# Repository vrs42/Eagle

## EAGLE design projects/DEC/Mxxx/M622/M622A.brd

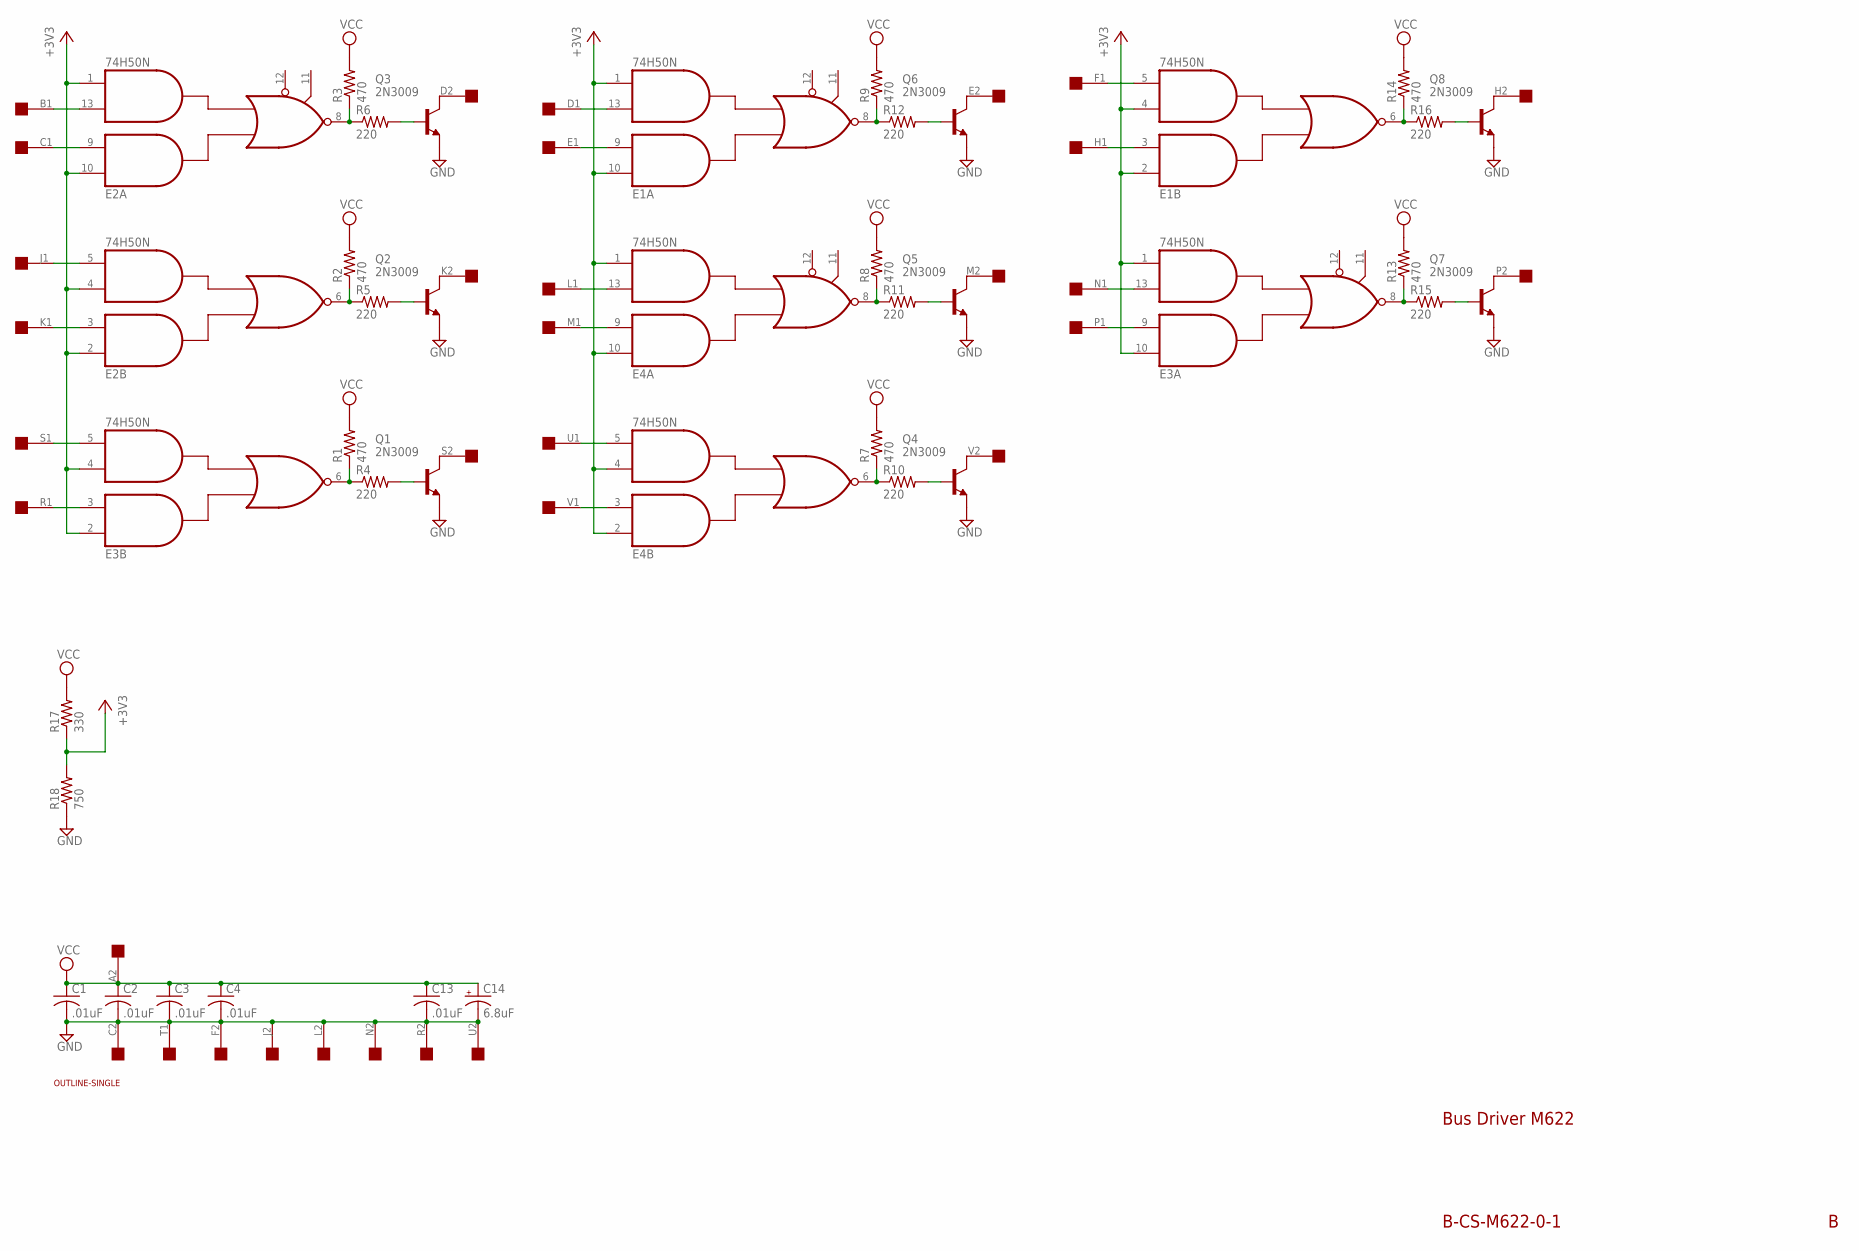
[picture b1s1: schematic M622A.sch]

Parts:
C1, C2, C3, C4, C13: .01uF; C050-025X075
C14: 6.8uF; E12-8
E1, E2, E3, E4: 74H50N; DIL14
Q1, Q2, Q3, Q4, Q5, Q6, Q7, Q8: 2N3009; TO5
R1, R2, R3, R7, R8, R9, R13, R14: 470; 0207/10
R4, R5, R6, R10, R11, R12, R15, R16: 220; 0207/10
R17: 330; 0207/10
R18: 750; 0207/10
U$1: SINGLE; EDGE-CON2
U$4: OUTLINE-SINGLE; SINGLE

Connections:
+3V3: E1.1 (I4), E1.2 (I1), E1.4 (I3), E1.10 (I1), E2.1 (I4), E2.2 (I1), E2.4 (I3), E2.10 (I1), E3.1 (I4), E3.2 (I1), E3.4 (I3), E3.10 (I1), E4.1 (I4), E4.2 (I1), E4.4 (I3), E4.10 (I1), R17.1, R18.2
GND: C1.2, C2.2, C3.2, C4.2, C13.2, C14.-, E1.7 (GND), E2.7 (GND), E3.7 (GND), E4.7 (GND), Q1.1 (E), Q2.1 (E), Q3.1 (E), Q4.1 (E), Q5.1 (E), Q6.1 (E), Q7.1 (E), Q8.1 (E), R18.1, U$1.C2, U$1.F2, U$1.J2, U$1.L2, U$1.N2, U$1.R2, U$1.T1, U$1.U2
unnamed: E2.3 (I2), U$1.K1
unnamed: E2.5 (I4), U$1.J1
unnamed: E2.9 (I2), U$1.C1
unnamed: E2.13 (I3), U$1.B1
unnamed: E3.5 (I4), U$1.S1
unnamed: E3.3 (I2), U$1.R1
unnamed: E2.8 (O), R3.1, R6.1
unnamed: Q3.2 (B), R6.2
unnamed: E1.8 (O), R9.1, R12.1
unnamed: Q6.2 (B), R12.2
unnamed: Q3.3 (C), U$1.D2
unnamed: E2.6 (O), R2.1, R5.1
unnamed: Q6.3 (C), U$1.E2
unnamed: E4.3 (I2), U$1.V1
unnamed: E4.5 (I4), U$1.U1
unnamed: E4.13 (I3), U$1.L1
unnamed: E4.9 (I2), U$1.M1
unnamed: Q2.2 (B), R5.2
unnamed: E1.6 (O), R14.1, R16.1
unnamed: Q8.2 (B), R16.2
unnamed: E4.8 (O), R8.1, R11.1
unnamed: Q5.2 (B), R11.2
unnamed: E3.8 (O), R13.1, R15.1
unnamed: Q7.2 (B), R15.2
unnamed: E3.6 (O), R1.1, R4.1
unnamed: Q1.2 (B), R4.2
unnamed: E4.6 (O), R7.1, R10.1
unnamed: Q4.2 (B), R10.2
unnamed: E1.13 (I3), U$1.D1
unnamed: E1.9 (I2), U$1.E1
unnamed: Q5.3 (C), U$1.M2
unnamed: Q4.3 (C), U$1.V2
unnamed: E1.5 (I4), U$1.F1
unnamed: E3.9 (I2), U$1.P1
unnamed: E3.13 (I3), U$1.N1
unnamed: E1.3 (I2), U$1.H1
unnamed: Q8.3 (C), U$1.H2
unnamed: Q7.3 (C), U$1.P2
unnamed: Q1.3 (C), U$1.S2
unnamed: Q2.3 (C), U$1.K2
VCC: C1.1, C2.1, C3.1, C4.1, C13.1, C14.+, E1.14 (VCC), E2.14 (VCC), E3.14 (VCC), E4.14 (VCC), R1.2, R2.2, R3.2, R7.2, R8.2, R9.2, R13.2, R14.2, R17.2, U$1.A2

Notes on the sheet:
Bus Driver M622
B-CS-M622-0-1

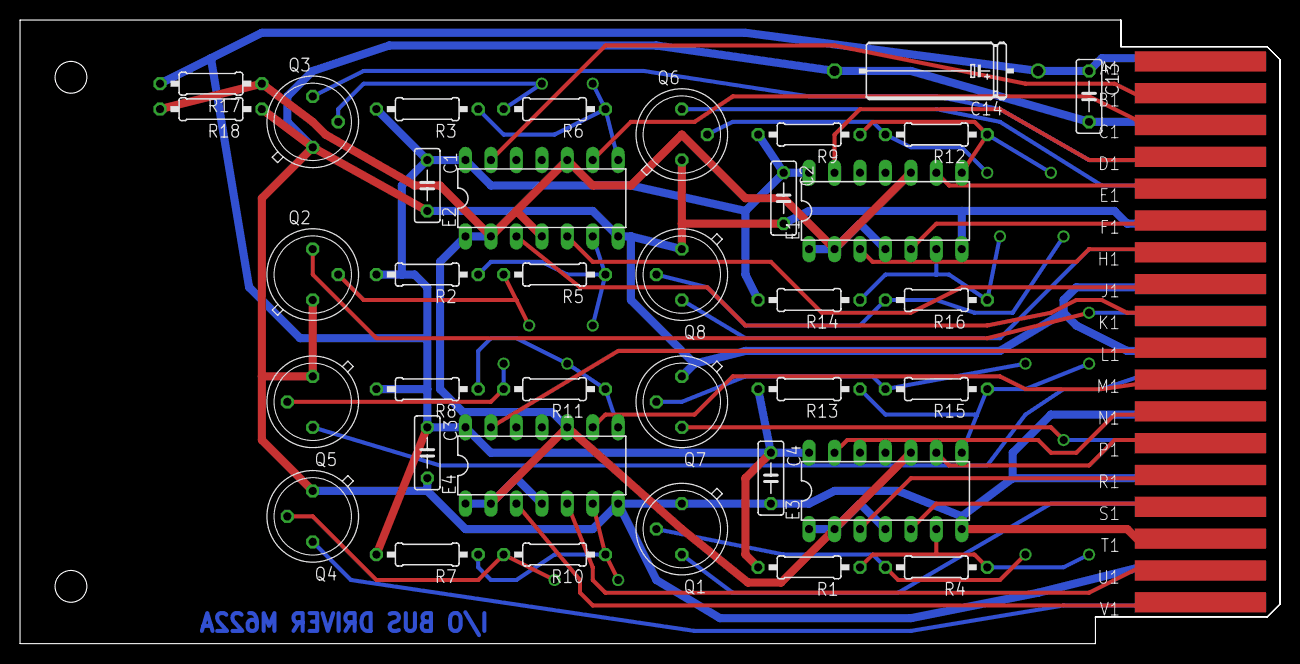
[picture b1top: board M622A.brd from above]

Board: 2 copper layers, 125.7 x 62.2 mm, 38 parts (0 on the bottom side), 43 nets.

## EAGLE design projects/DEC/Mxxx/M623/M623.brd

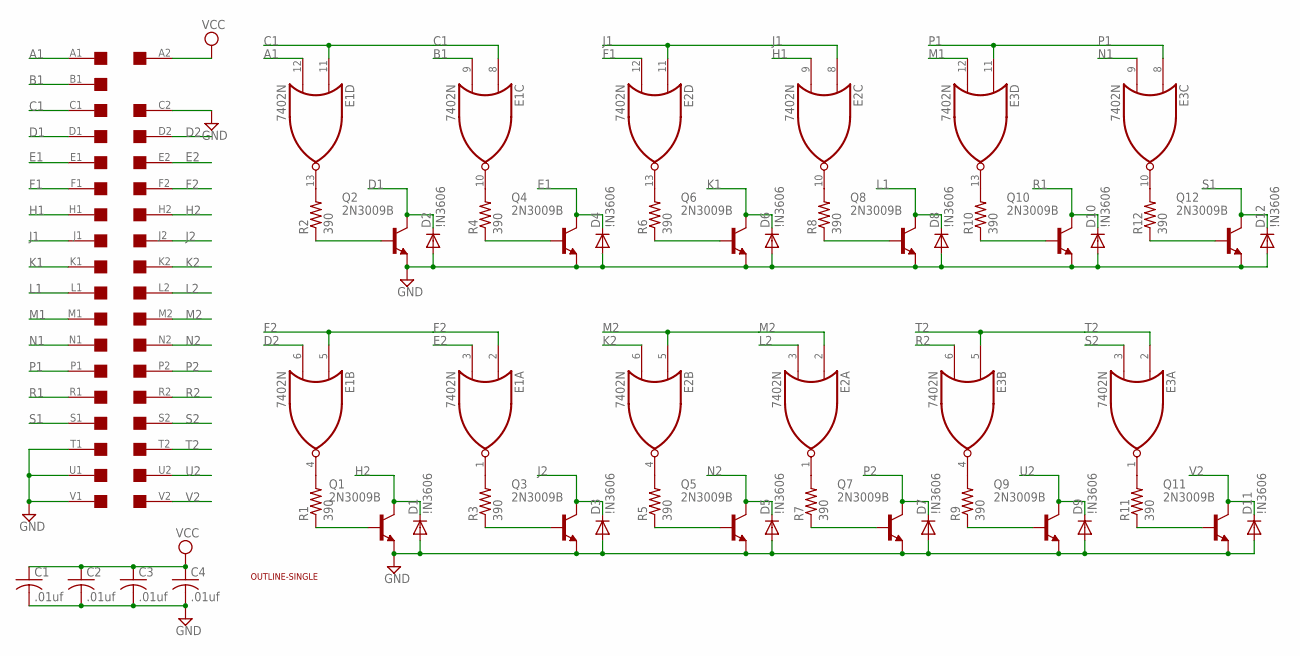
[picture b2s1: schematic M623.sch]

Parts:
C1, C2, C3, C4: .01uf; C050-025X075
D1, D2, D3, D4, D5, D6, D7, D8, D9, D10, D11, D12: \!N3606; DO35-10
E1, E2, E3: 7402N; DIL14
Q1, Q2, Q3, Q4, Q5, Q6, Q7, Q8, Q9, Q10, Q11, Q12: 2N3009B; TO39
R1, R2, R3, R4, R5, R6, R7, R8, R9, R10, R11, R12: 390; 0207/10
U$1: OUTLINE-SINGLE; SINGLE
U$4: SINGLE; EDGE-CON2

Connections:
A1: E1.12 (I1), U$4.A1
B1: E1.9 (I1), U$4.B1
C1: E1.8 (I0), E1.11 (I0), U$4.C1
D1: D2.C, Q2.3 (C), U$4.D1
D2: E1.6 (I1), U$4.D2
E1: D4.C, Q4.3 (C), U$4.E1
E2: E1.3 (I1), U$4.E2
F1: E2.12 (I1), U$4.F1
F2: E1.2 (I0), E1.5 (I0), U$4.F2
GND: C1.2, C2.2, C3.2, C4.2, D1.A, D2.A, D3.A, D4.A, D5.A, D6.A, D7.A, D8.A, D9.A, D10.A, D11.A, D12.A, E1.7 (GND), E2.7 (GND), E3.7 (GND), Q1.1 (E), Q2.1 (E), Q3.1 (E), Q4.1 (E), Q5.1 (E), Q6.1 (E), Q7.1 (E), Q8.1 (E), Q9.1 (E), Q10.1 (E), Q11.1 (E), Q12.1 (E), U$4.C2, U$4.T1, U$4.U1, U$4.V1
H1: E2.9 (I1), U$4.H1
H2: D1.C, Q1.3 (C), U$4.H2
J1: E2.8 (I0), E2.11 (I0), U$4.J1
J2: D3.C, Q3.3 (C), U$4.J2
K1: D6.C, Q6.3 (C), U$4.K1
K2: E2.6 (I1), U$4.K2
L1: D8.C, Q8.3 (C), U$4.L1
L2: E2.3 (I1), U$4.L2
M1: E3.12 (I1), U$4.M1
M2: E2.2 (I0), E2.5 (I0), U$4.M2
N1: E3.9 (I1), U$4.N1
N2: D5.C, Q5.3 (C), U$4.N2
unnamed: E1.13 (O), R2.2
unnamed: Q2.2 (B), R2.1
unnamed: E1.4 (O), R1.2
unnamed: Q1.2 (B), R1.1
unnamed: E1.10 (O), R4.2
unnamed: E1.1 (O), R3.2
unnamed: E2.4 (O), R5.2
unnamed: E2.13 (O), R6.2
unnamed: E2.1 (O), R7.2
unnamed: E2.10 (O), R8.2
unnamed: E3.4 (O), R9.2
unnamed: E3.13 (O), R10.2
unnamed: E3.1 (O), R11.2
unnamed: E3.10 (O), R12.2
unnamed: Q12.2 (B), R12.1
unnamed: Q4.2 (B), R4.1
unnamed: Q6.2 (B), R6.1
unnamed: Q8.2 (B), R8.1
unnamed: Q10.2 (B), R10.1
unnamed: Q3.2 (B), R3.1
unnamed: Q5.2 (B), R5.1
unnamed: Q7.2 (B), R7.1
unnamed: Q9.2 (B), R9.1
unnamed: Q11.2 (B), R11.1
P1: E3.8 (I0), E3.11 (I0), U$4.P1
P2: D7.C, Q7.3 (C), U$4.P2
R1: D10.C, Q10.3 (C), U$4.R1
R2: E3.6 (I1), U$4.R2
S1: D12.C, Q12.3 (C), U$4.S1
S2: E3.3 (I1), U$4.S2
T2: E3.2 (I0), E3.5 (I0), U$4.T2
U2: D9.C, Q9.3 (C), U$4.U2
V2: D11.C, Q11.3 (C), U$4.V2
VCC: C1.1, C2.1, C3.1, C4.1, E1.14 (VCC), E2.14 (VCC), E3.14 (VCC), U$4.A2

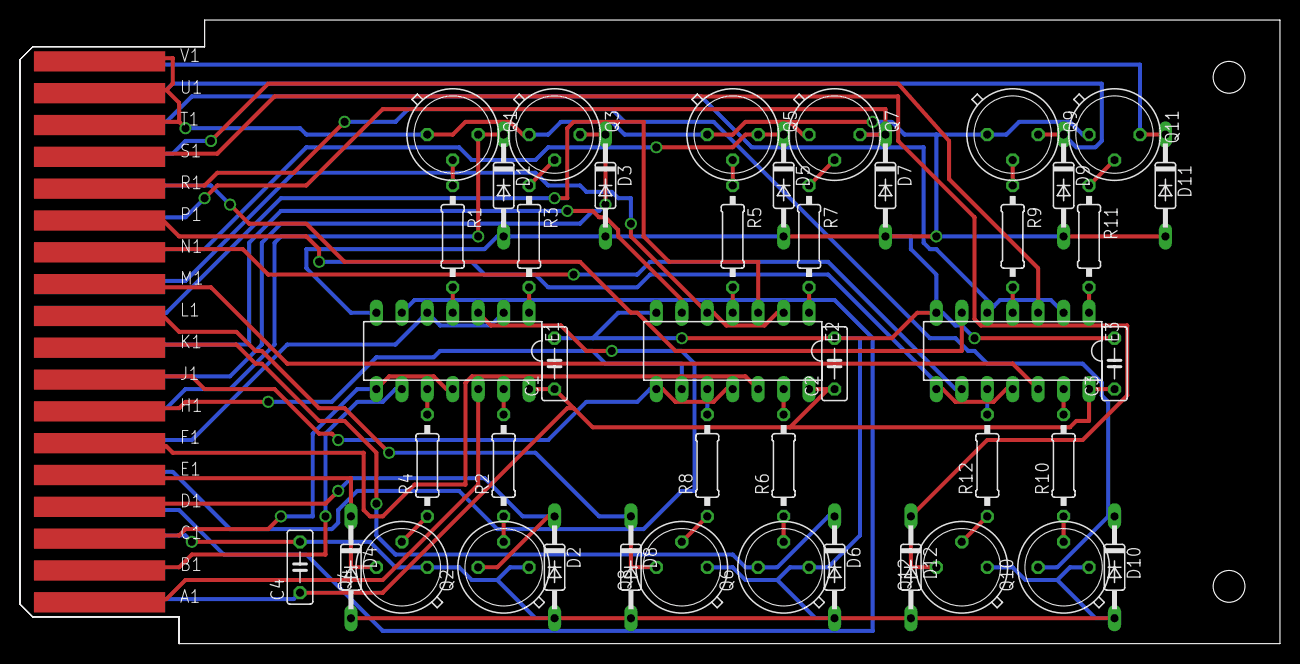
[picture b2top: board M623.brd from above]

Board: 2 copper layers, 125.7 x 62.2 mm, 45 parts (0 on the bottom side), 56 nets.

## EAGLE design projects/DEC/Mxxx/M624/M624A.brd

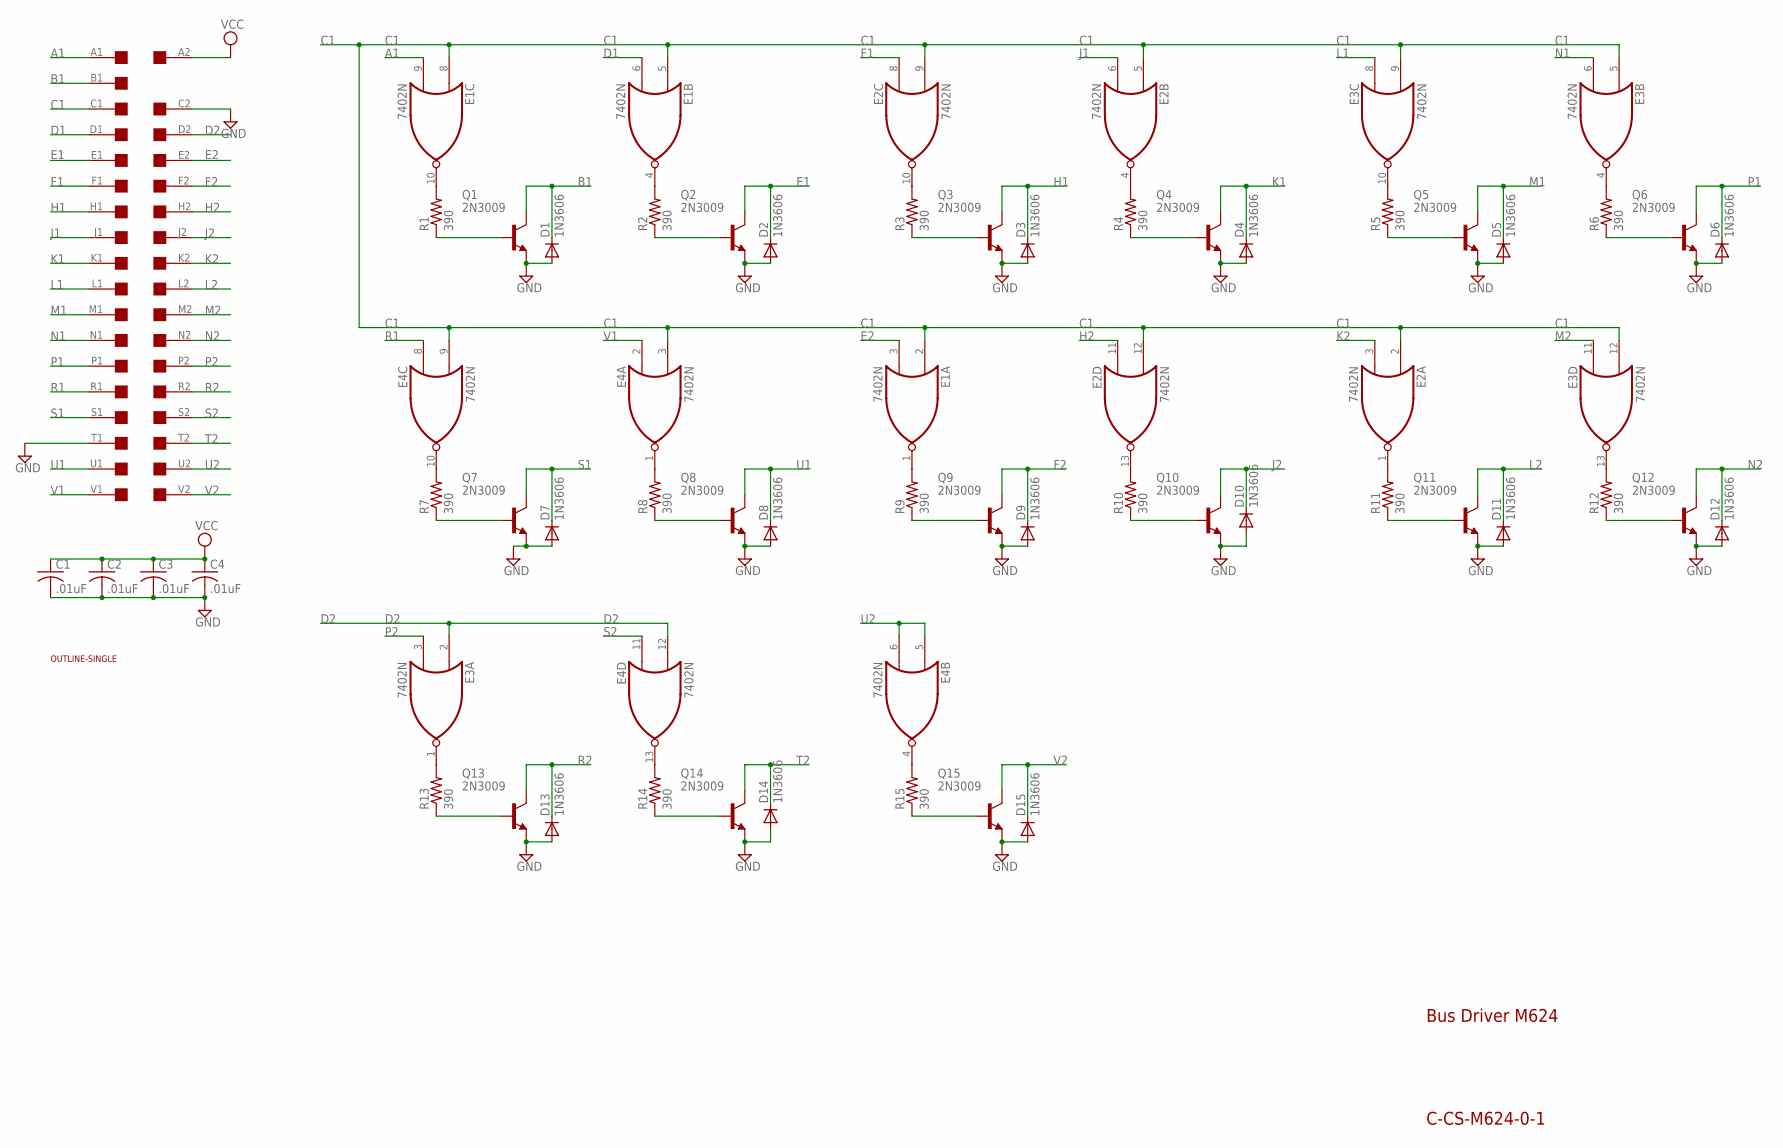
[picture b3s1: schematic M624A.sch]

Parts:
C1, C2, C3, C4: .01uF; C050-025X075
D1, D2, D3, D4, D5, D6, D7, D8, D9, D10, D11, D12, D13, D14, D15: 1N3606; DO35-10
E1, E2, E3, E4: 7402N; DIL14
Q1, Q2, Q3, Q4, Q5, Q6, Q7, Q8, Q9, Q10, Q11, Q12, Q13, Q14, Q15: 2N3009; TO39
R1, R2, R3, R4, R5, R6, R7, R8, R9, R10, R11, R12, R13, R14, R15: 390; 0207/10
U$1: OUTLINE-SINGLE; SINGLE
U$4: SINGLE; EDGE-CON2

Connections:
A1: E1.9 (I1), U$4.A1
B1: D1.C, Q1.3 (C), U$4.B1
C1: E1.2 (I0), E1.5 (I0), E1.8 (I0), E2.2 (I0), E2.5 (I0), E2.9 (I1), E2.12 (I1), E3.5 (I0), E3.9 (I1), E3.12 (I1), E4.3 (I1), E4.9 (I1), U$4.C1
D1: E1.6 (I1), U$4.D1
D2: E3.2 (I0), E4.12 (I1), U$4.D2
E1: D2.C, Q2.3 (C), U$4.E1
E2: E1.3 (I1), U$4.E2
F1: E2.8 (I0), U$4.F1
F2: D9.C, Q9.3 (C), U$4.F2
GND: C1.2, C2.2, C3.2, C4.2, D1.A, D2.A, D3.A, D4.A, D5.A, D6.A, D7.A, D8.A, D9.A, D10.A, D11.A, D12.A, D13.A, D14.A, D15.A, E1.7 (GND), E2.7 (GND), E3.7 (GND), E4.7 (GND), Q1.1 (E), Q2.1 (E), Q3.1 (E), Q4.1 (E), Q5.1 (E), Q6.1 (E), Q7.1 (E), Q8.1 (E), Q9.1 (E), Q10.1 (E), Q11.1 (E), Q12.1 (E), Q13.1 (E), Q14.1 (E), Q15.1 (E), U$4.C2, U$4.T1
H1: D3.C, Q3.3 (C), U$4.H1
H2: E2.11 (I0), U$4.H2
J1: E2.6 (I1), U$4.J1
J2: D10.C, Q10.3 (C), U$4.J2
K1: D4.C, Q4.3 (C), U$4.K1
K2: E2.3 (I1), U$4.K2
L1: E3.8 (I0), U$4.L1
L2: D11.C, Q11.3 (C), U$4.L2
M1: D5.C, Q5.3 (C), U$4.M1
M2: E3.11 (I0), U$4.M2
N1: E3.6 (I1), U$4.N1
N2: D12.C, Q12.3 (C), U$4.N2
unnamed: E1.10 (O), R1.2
unnamed: Q1.2 (B), R1.1
unnamed: E4.10 (O), R7.2
unnamed: Q7.2 (B), R7.1
unnamed: E3.1 (O), R13.2
unnamed: E4.13 (O), R14.2
unnamed: E4.4 (O), R15.2
unnamed: Q13.2 (B), R13.1
unnamed: Q14.2 (B), R14.1
unnamed: Q15.2 (B), R15.1
unnamed: E1.4 (O), R2.2
unnamed: E4.1 (O), R8.2
unnamed: E1.1 (O), R9.2
unnamed: E2.10 (O), R3.2
unnamed: E2.13 (O), R10.2
unnamed: E2.4 (O), R4.2
unnamed: E2.1 (O), R11.2
unnamed: E3.10 (O), R5.2
unnamed: E3.13 (O), R12.2
unnamed: E3.4 (O), R6.2
unnamed: Q6.2 (B), R6.1
unnamed: Q2.2 (B), R2.1
unnamed: Q3.2 (B), R3.1
unnamed: Q4.2 (B), R4.1
unnamed: Q5.2 (B), R5.1
unnamed: Q8.2 (B), R8.1
unnamed: Q9.2 (B), R9.1
unnamed: Q10.2 (B), R10.1
unnamed: Q11.2 (B), R11.1
unnamed: Q12.2 (B), R12.1
P1: D6.C, Q6.3 (C), U$4.P1
P2: E3.3 (I1), U$4.P2
R1: E4.8 (I0), U$4.R1
R2: D13.C, Q13.3 (C), U$4.R2
S1: D7.C, Q7.3 (C), U$4.S1
S2: E4.11 (I0), U$4.S2
T2: D14.C, Q14.3 (C), U$4.T2
U1: D8.C, Q8.3 (C), U$4.U1
U2: E4.5 (I0), E4.6 (I1), U$4.U2
V1: E4.2 (I0), U$4.V1
V2: D15.C, Q15.3 (C), U$4.V2
VCC: C1.1, C2.1, C3.1, C4.1, E1.14 (VCC), E2.14 (VCC), E3.14 (VCC), E4.14 (VCC), U$4.A2

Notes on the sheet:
Bus Driver M624
C-CS-M624-0-1

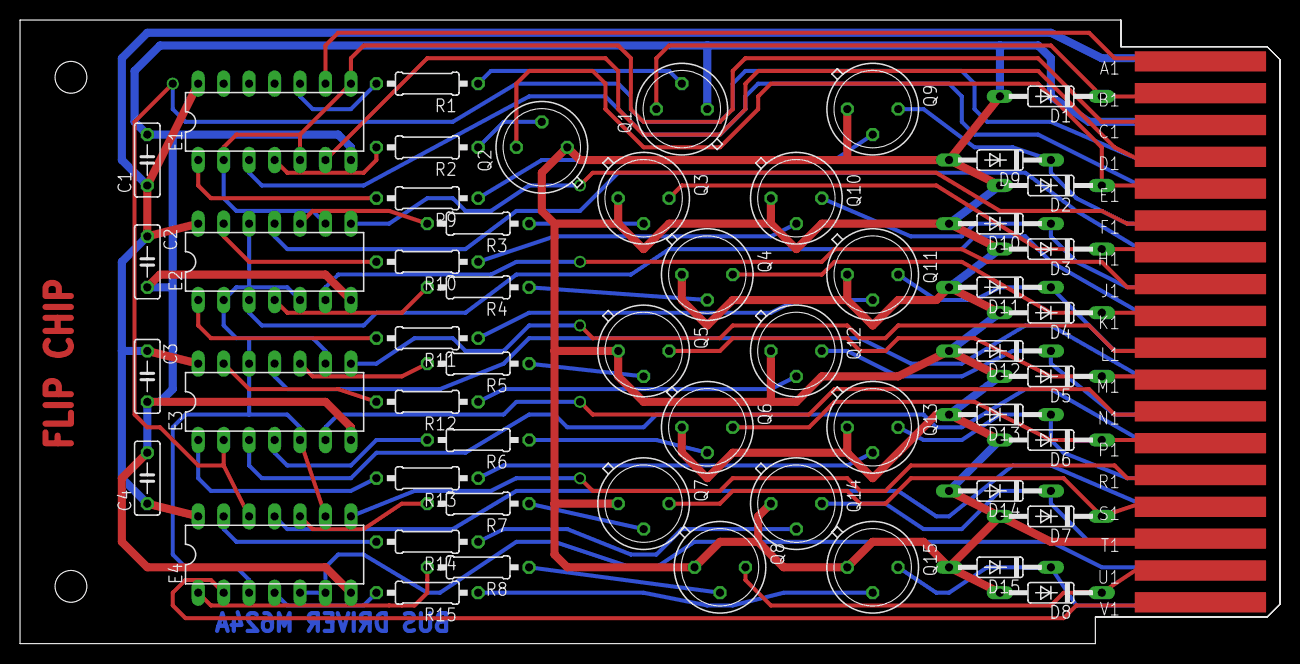
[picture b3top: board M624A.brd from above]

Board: 2 copper layers, 125.7 x 62.2 mm, 56 parts (0 on the bottom side), 64 nets.

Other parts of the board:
U$2: FLIPCHIP
